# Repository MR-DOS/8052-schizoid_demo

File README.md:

# 8052-schizoid_demo
My own improved implementation of so-called "Schizofreny" 8051 board.You can find the original version [here](http://www.bezstarosti.cz/jungle/schizofreny/schizofreny.htm). 

## Disclaimer
I would like to admit this is a very old project back when I was rather beginner at programming. It somehow survived (or, better to say, did not) being moved across several generations of my computers (about 6 notebooks, 3 desktops, one dead HDD and one HDD encrypted due to ransomware) ranging from PIII-M to 3rd gen i5. I had to visit my parents and search my old computer to get the sources of the PC part of the SW, which I thought have been destroyed long ago.

Since this is an old project, it will receive only very limited support from me.
On the other hand, the project worked and was *usable*. Well, if you call uC with no debug at all usable, that is.

## Brief info
### What this thingumabob consists of
Hardware: AT89C52 with 256B of internal RAM and bootloader (you can in fact use any 8051, just not 80C31), 64 kB of external ROM and 64 kB of external RAM (can be disabled).
Bootloader: Handles all of the programming part and communication with PC via virtual COM port over USB.

Terminal on PC: Communicates with the bootloader over USB. You just have to supply it with the HEX file to be programmed and number of the COM port. Originally, this was used to be integrated into MIDE (8051-centric dead simple IDE).

### How to use it
Hardware: Just build it, no calibration needed.

Bootloader: Program the 80C52 with the bootloader (you need to have a programmer).

Terminal: Use the batch script program.bat. It converts a HEX file into BIN file, sends it to the board and starts the program. It has two arguments, first is the name of the HEX file, second is number of COM port (just a number, like "5", not "COM5").

### MIDE-51 integration
I originally used MIDE-51 for development of the bootloader. Now, I would not recommend the IDE to anyone since it has no autocompletion and next to no connection with the toolchain. However if you wish to use it, here is how to set it up.

* The line with name "execute file" should point to program.bat (8052term.exe and hex2bin.exe have to be in the same directory).
* Parameter 2 specifies number of COM port to which the demoboard is connected.
* MIDE-51 can be downloaded from [here](http://www.opcube.com/home.html#MIDE51).

## Technical info
This "Schizofreny" inspired board uses 128 kB SRAM to emulate 64 kB of ROM and 64 kB of RAM. The program is sent to the board via virtual COM port (CH340G) over USB. Internal bootloader and dedicated circuitry around the 8052 (AT89C52, specifically) handles all of the access to the SRAM during programming. One of the RS232 control signals resets the CPU, another switches it between the bootloader and user mode. Each mode has its own crystal, so the board can be used at any frequency.

The virtual 64 kB RAM portion of the 128 kB SRAM can be disabled so it does not interfere with anything connected to the board. In this mode, ports P1 and P3 are completely free for the user. When the RAM is not disabled, P1 is free, but P3 has P3.6, P3.7 used for RD, WR (access to RAM). The board handles disconnecting of these pins from the header, so it does not interfere with user HW.
To sum it up, you have either 14 or 16 GPIO accessible dependng on the mode (set by jumper).

Sadly, the virtual ROM sits on ports P0 and P2, so it is not possible to use them for anything else. Since the 8052 has 256 bytes of RAM and Flash cannot be reflashed using bootloader, there is no other way to load the program. This is a limitation of the 8051 architecture.

### What was used for the project
The board was made in EAGLE. For those not willing to pay for this shitware to make this board, vector graphics with the board TOP and BOTTOM layers, as well as the schematic, BOM and drawing of placement of parts, are included.

The bootloader was written in C and can be compiled using SDCC. Do not even try with GCC (it does not even have a useable port for 8051, at least not one I'm aware of).

The terminal was written using C (GCC / MinGW) for Windows. It uses RS-232 library from Teunis van Beelen, licensed under GNU GPL, can be found [here](https://www.teuniz.net/RS-232/index.html). If you would like to compile the terminal yourself, you should first check the author's website whether there is a new version of the library.

### Where to find the resources
* The Eagle project is in **HW_eagle**
* The preview of the board, BOM, top and bottom copper layers in PostScript, PDF and SVG and schematics are in **HW_makedata**
* The bootloader is located in **SW_8052_bootloader**. The BIN and HEX files are located in **SW_8052_bootloader/bin/**, sources are in **SW_8052_bootloader/src/**
* The terminal is located in **8052-schizoid_demo/SW_PC_terminal**. The binaries are in **8052-schizoid_demo/SW_PC_terminal/bin**, the sources are in **8052-schizoid_demo/SW_PC_terminal/src**

## Known bugs
* Upon sending the binary to the board, the board responds with some messages saying that the transfer completed. However, prior to that, the board sends one seemingly random character. This is a bug in the main while(1) loop where it waits upon completion of the code loading and then it parses the last character in the buffer as unknown control character and thus is sent back. It has no effect on functionality, but it looks stupid. This should be corrected later.
* There is no image of the finished board. I will add some later.
* It looks like the SVG files are shown correctly in Inkscape, but not in LXDE default image viewer. This should be checked.

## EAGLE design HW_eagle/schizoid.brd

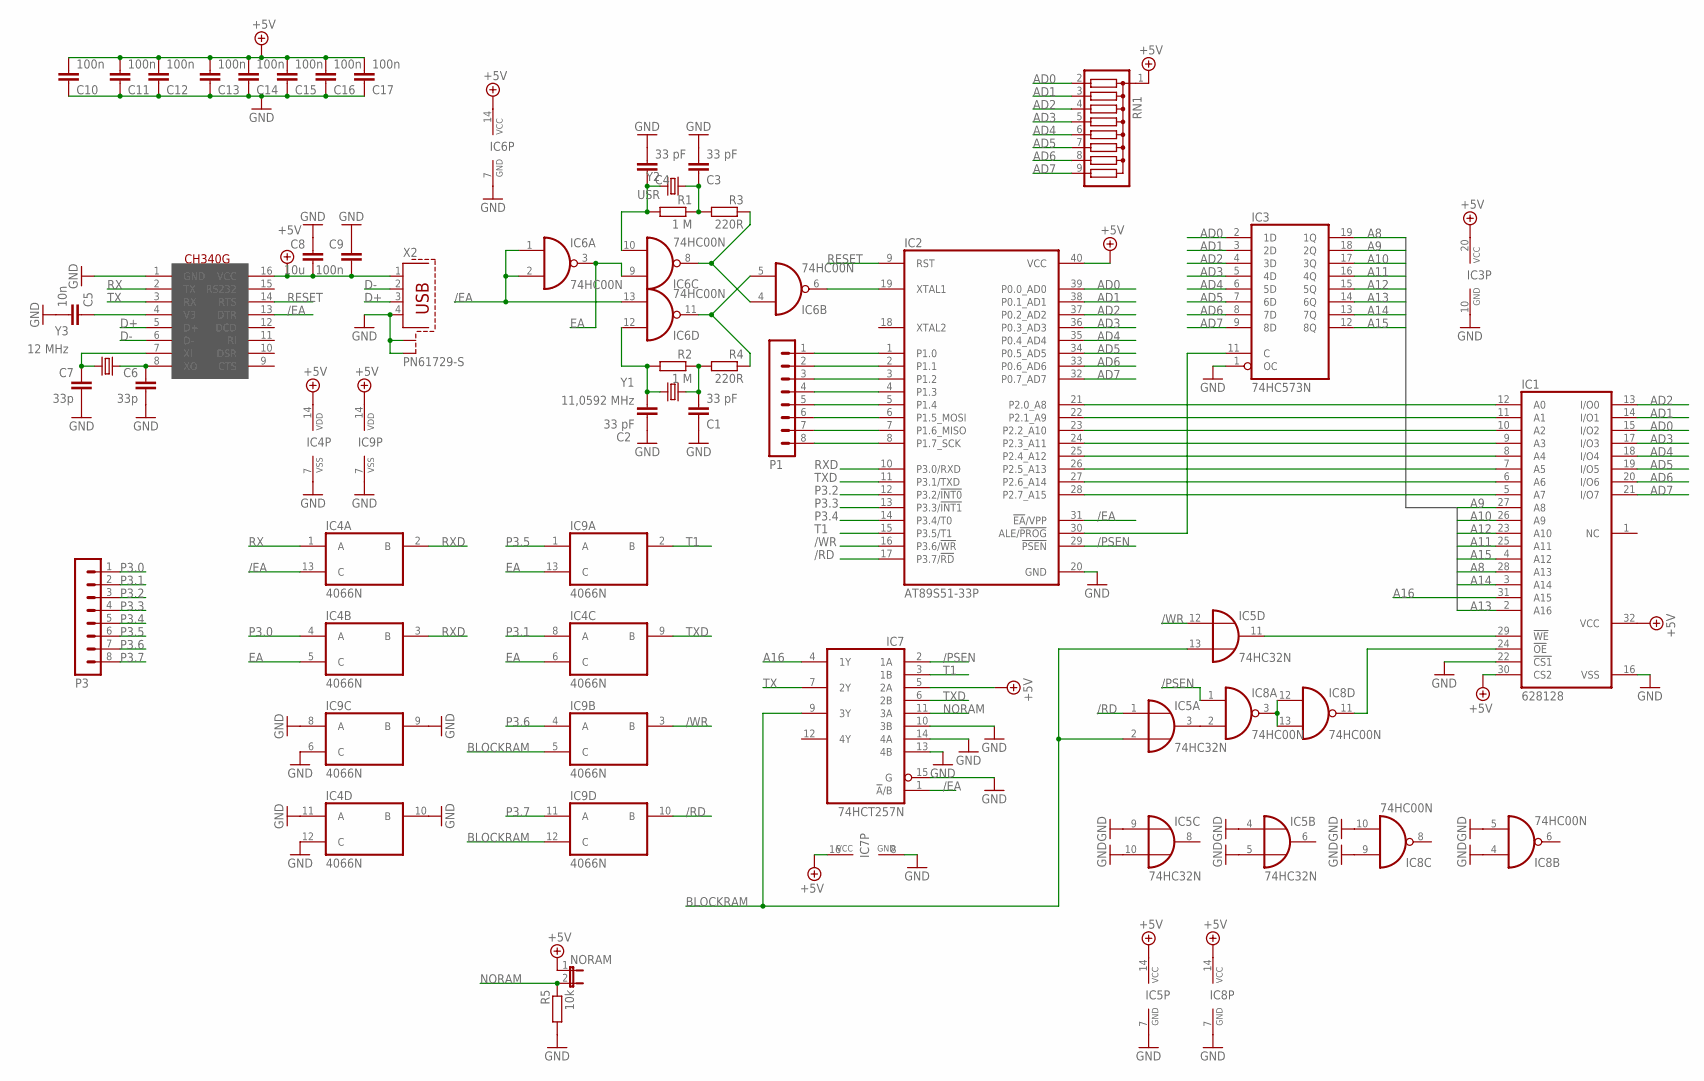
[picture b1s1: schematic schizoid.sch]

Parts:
C1, C2, C3, C4: 33 pF; C025-025X050
C5: 10n; C025-025X050
C6, C7: 33p; C025-025X050
C8: 10u; C025-025X050
C9, C10, C11, C12, C13, C14, C15, C16, C17: 100n; C025-025X050
IC1: 628128; DIL32
IC2: AT89S51-33P; DIL40
IC3: 74HC573N; DIL20
IC4, IC9: 4066N; DIL14
IC5: 74HC32N; DIL14
IC6, IC8: 74HC00N; DIL14
IC7: 74HCT257N; DIL16
NORAM: JP1E; JP1
P1, P3: MA08-1
R1, R2: 1 M; 0207/7
R3, R4: 220R; 0207/7
R5: 10k; 0207/7
RN1: G08R; SIL9
U$1: CH340G; SOIC16
X2: PN61729-S
Y1: 11,0592 MHz; HC49U-V
Y2: USR; HC49U-V
Y3: 12 MHz; HC49U-V

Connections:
+5V: C8.2, C9.2, C10.2, C11.2, C12.2, C13.2, C14.2, C15.2, C16.2, C17.2, IC1.30 (CS2), IC1.32 (VCC), IC2.40 (VCC), IC3.20 (VCC), IC4.14 (VDD), IC5.14 (VCC), IC6.14 (VCC), IC7.5 (2A), IC7.16 (VCC), IC8.14 (VCC), IC9.14 (VDD), NORAM.1, RN1.1, U$1.16 (VCC), X2.1
/EA: IC2.31 (!EA!/VPP), IC4.13 (C), IC6.1 (I0), IC6.2 (I1), IC6.13 (I1), IC7.1 (!A!/B), U$1.13 (DTR)
/PSEN: IC2.29 (!PSEN), IC7.2 (1A), IC8.1 (I0)
/RD: IC2.17 (P3.7/!RD), IC5.1 (I0), IC9.10 (B)
/WR: IC2.16 (P3.6/!WR), IC5.12 (I0), IC9.3 (B)
A8: IC1.28 (A13), IC3.19 (1Q)
A9: IC1.27 (A8), IC3.18 (2Q)
A10: IC1.26 (A9), IC3.17 (3Q)
A11: IC1.25 (A11), IC3.16 (4Q)
A12: IC1.23 (A10), IC3.15 (5Q)
A13: IC1.2 (A16), IC3.14 (6Q)
A14: IC1.3 (A14), IC3.13 (7Q)
A15: IC1.4 (A12), IC3.12 (8Q)
A16: IC1.31 (A15), IC7.4 (1Y)
AD0: IC1.15 (I/O2), IC2.39 (P0.0_AD0), IC3.2 (1D), RN1.2
AD1: IC1.14 (I/O1), IC2.38 (P0.1_AD1), IC3.3 (2D), RN1.3
AD2: IC1.13 (I/O0), IC2.37 (P0.2_AD2), IC3.4 (3D), RN1.4
AD3: IC1.17 (I/O3), IC2.36 (P0.3_AD3), IC3.5 (4D), RN1.5
AD4: IC1.18 (I/O4), IC2.35 (P0.4_AD4), IC3.6 (5D), RN1.6
AD5: IC1.19 (I/O5), IC2.34 (P0.5_AD5), IC3.7 (6D), RN1.7
AD6: IC1.20 (I/O6), IC2.33 (P0.6_AD6), IC3.8 (7D), RN1.8
AD7: IC1.21 (I/O7), IC2.32 (P0.7_AD7), IC3.9 (8D), RN1.9
BLOCKRAM: IC5.2 (I1), IC5.13 (I1), IC7.9 (3Y), IC9.5 (C), IC9.12 (C)
D+: U$1.5 (D+), X2.3
D-: U$1.6 (D-), X2.2
EA: IC4.5 (C), IC4.6 (C), IC6.3 (O), IC6.9 (I0), IC9.13 (C)
GND: C1.1, C2.1, C3.2, C4.2, C5.2, C6.2, C7.2, C8.1, C9.1, C10.1, C11.1, C12.1, C13.1, C14.1, C15.1, C16.1, C17.1, IC1.16 (VSS), IC1.22 (!CS1), IC2.20 (GND), IC3.1 (OC), IC3.10 (GND), IC4.7 (VSS), IC4.10 (B), IC4.11 (A), IC4.12 (C), IC5.4 (I0), IC5.5 (I1), IC5.7 (GND), IC5.9 (I0), IC5.10 (I1), IC6.7 (GND), IC7.8 (GND), IC7.10 (3B), IC7.13 (4B), IC7.14 (4A), IC7.15 (G), IC8.4 (I0), IC8.5 (I1), IC8.7 (GND), IC8.9 (I0), IC8.10 (I1), IC9.6 (C), IC9.7 (VSS), IC9.8 (A), IC9.9 (B), R5.2, U$1.1 (GND), X2.4, X2.S1, X2.S2
unnamed: IC1.12 (A0), IC2.21 (P2.0_A8)
unnamed: IC1.11 (A1), IC2.22 (P2.1_A9)
unnamed: IC1.10 (A2), IC2.23 (P2.2_A10)
unnamed: IC1.9 (A3), IC2.24 (P2.3_A11)
unnamed: IC1.8 (A4), IC2.25 (P2.4_A12)
unnamed: IC1.7 (A5), IC2.26 (P2.5_A13)
unnamed: IC1.6 (A6), IC2.27 (P2.6_A14)
unnamed: IC1.5 (A7), IC2.28 (P2.7_A15)
unnamed: IC2.30 (ALE/!PROG), IC3.11 (C)
unnamed: C3.1, R1.1, R3.2, Y2.1
unnamed: IC2.1 (P1.0), P1.1
unnamed: C1.2, R2.1, R4.2, Y1.1
unnamed: IC2.2 (P1.1), P1.2
unnamed: IC2.3 (P1.2), P1.3
unnamed: IC2.4 (P1.3), P1.4
unnamed: IC2.5 (P1.4), P1.5
unnamed: IC2.6 (P1.5_MOSI), P1.6
unnamed: IC2.7 (P1.6_MISO), P1.7
unnamed: IC5.3 (O), IC8.2 (I1)
unnamed: IC6.4 (I0), IC6.8 (O), R3.1
unnamed: IC8.3 (O), IC8.12 (I0), IC8.13 (I1)
unnamed: IC6.5 (I1), IC6.11 (O), R4.1
unnamed: C2.2, IC6.12 (I0), R2.2, Y1.2
unnamed: IC2.8 (P1.7_SCK), P1.8
unnamed: C4.1, IC6.10 (I1), R1.2, Y2.2
unnamed: IC2.19 (XTAL1), IC6.6 (O)
unnamed: C5.1, U$1.4 (V3)
unnamed: C6.1, U$1.8 (XO), Y3.1
unnamed: C7.1, U$1.7 (XI), Y3.2
unnamed: IC1.29 (!WE), IC5.11 (O)
unnamed: IC1.24 (!OE), IC8.11 (O)
NORAM: IC7.11 (3A), NORAM.2, R5.1
P3.0: IC4.4 (A), P3.1
P3.1: IC4.8 (A), P3.2
P3.2: IC2.12 (P3.2/!INT0), P3.3
P3.3: IC2.13 (P3.3/!INT1), P3.4
P3.4: IC2.14 (P3.4/T0), P3.5
P3.5: IC9.1 (A), P3.6
P3.6: IC9.4 (A), P3.7
P3.7: IC9.11 (A), P3.8
RESET: IC2.9 (RST), U$1.14 (RTS)
RX: IC4.1 (A), U$1.2 (TX)
RXD: IC2.10 (P3.0/RXD), IC4.2 (B), IC4.3 (B)
T1: IC2.15 (P3.5/T1), IC7.3 (1B), IC9.2 (B)
TX: IC7.7 (2Y), U$1.3 (RX)
TXD: IC2.11 (P3.1/TXD), IC4.9 (B), IC7.6 (2B)

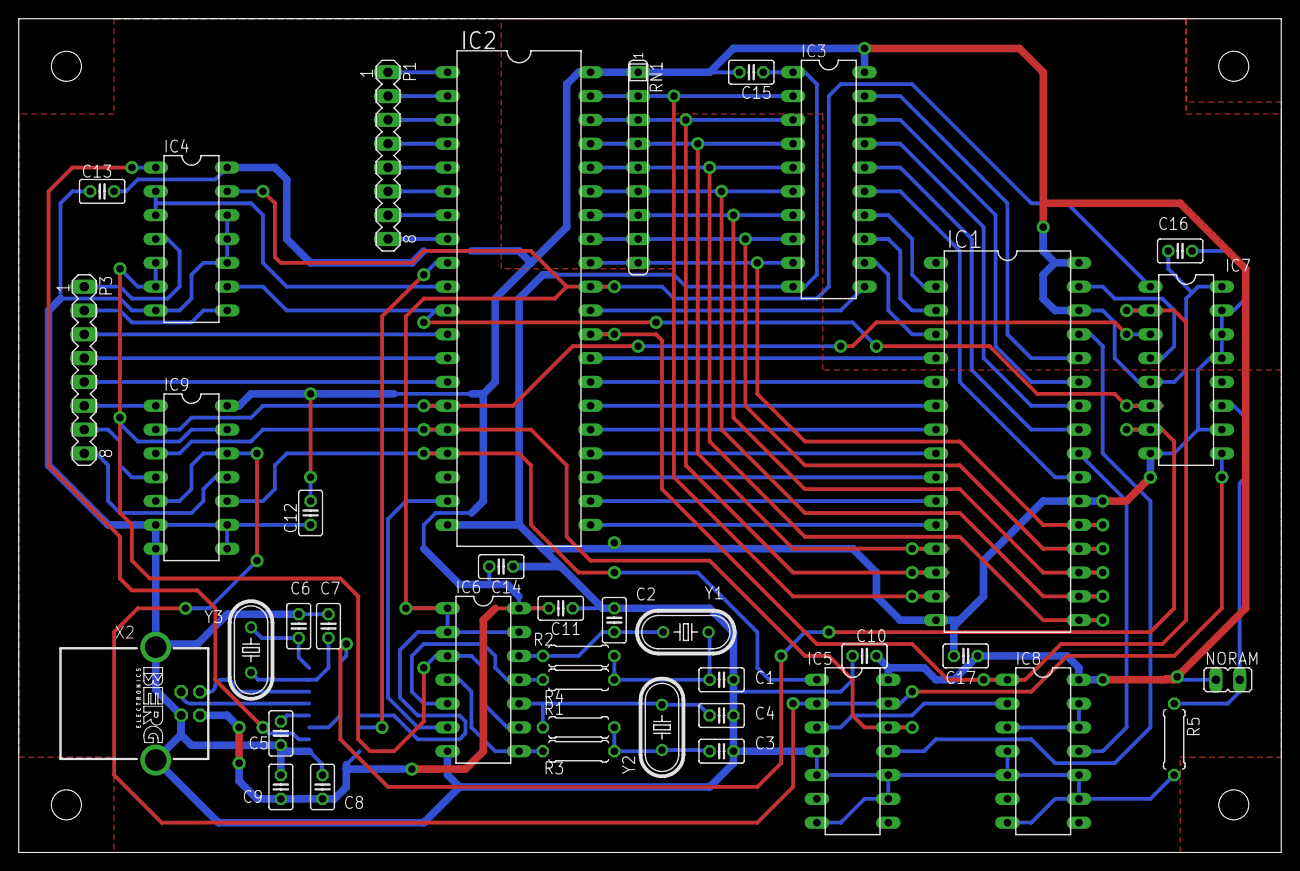
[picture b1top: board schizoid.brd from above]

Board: 2 copper layers, 134.6 x 88.9 mm, 40 parts (1 on the bottom side), 73 nets.

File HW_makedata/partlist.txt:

Partlist

Exported from schizoid.brd at 3/31/2018 4:59 PM

EAGLE Version 7.6.0 Copyright (c) 1988-2016 CadSoft

Assembly variant: 

Part     Value          Package      Library           Position (inch)       Orientation

C1       33 pF          C025-025X050 rcl               (2.95 0.725)          R180
C2       33 pF          C025-025X050 rcl               (2.5 0.975)           R270
C3       33 pF          C025-025X050 rcl               (2.95 0.425)          R0
C4       33 pF          C025-025X050 rcl               (2.95 0.575)          R0
C5       10n            C025-025X050 rcl               (1.1 0.5)             R270
C6       33p            C025-025X050 rcl               (1.175 0.95)          R90
C7       33p            C025-025X050 rcl               (1.3 0.95)            R90
C8       10u            C025-025X050 rcl               (1.275 0.275)         R270
C9       100n           C025-025X050 rcl               (1.1 0.275)           R270
C10      100n           C025-025X050 rcl               (3.55 0.825)          R0
C11      100n           C025-025X050 rcl               (2.275 1.025)         R180
C12      100n           C025-025X050 rcl               (1.225 1.425)         R90
C13      100n           C025-025X050 rcl               (0.35 2.775)          R0
C14      100n           C025-025X050 rcl               (2.025 1.2)           R180
C15      100n           C025-025X050 rcl               (3.075 3.275)         R180
C16      100n           C025-025X050 rcl               (4.875 2.525)         R180
C17      100n           C025-025X050 rcl               (3.975 0.825)         R0
IC1      628128         DIL32        memory-hitachi    (4.15 1.725)          R270
IC2      AT89S51-33P    DIL40        atmel             (2.1 2.325)           R270
IC3      74HC573N       DIL20        74xx-eu           (3.4 2.825)           R270
IC4      4066N          DIL14        40xx              (0.725 2.575)         R270
IC5      74HC32N        DIL14        74xx-eu           (3.5 0.425)           R270
IC6      74HC00N        DIL14        74xx-eu           (1.95 0.725)          R270
IC7      74HCT257N      DIL16        74xx-eu           (4.9 2.025)           R270
IC8      74HC00N        DIL14        74xx-eu           (4.3 0.425)           R270
IC9      4066N          DIL14        40xx              (0.725 1.575)         R270
NORAM                   JP1          jumper            (5.075 0.725)         R270
P1                      MA08-1       con-lstb          (1.55 2.925)          R270
P3                      MA08-1       con-lstb          (0.275 2.025)         R270
R1       1 M            0207/7       rcl               (2.35 0.525)          R180
R2       1 M            0207/7       rcl               (2.35 0.825)          R180
R3       220R           0207/7       rcl               (2.35 0.425)          R0
R4       220R           0207/7       rcl               (2.35 0.725)          R0
R5       10k            0207/7       rcl               (4.85 0.475)          R270
RN1                     SIL9         resistor-sil      (2.6 2.875)           R270
U$1      CH340G         SOIC16       usb-serial        (1.325 0.6)           MR90
X2       PN61729-S      PN61729-S    con-berg          (0.575 0.625)         R270
Y1       11,0592 MHz    HC49U-V      SparkFun-FreqCtrl (2.8 0.925)           R180
Y2       USR            HC49U-V      SparkFun-FreqCtrl (2.7 0.525)           R90
Y3       12 MHz         HC49U-V      SparkFun-FreqCtrl (0.975 0.85)          R270

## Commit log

2018-03-31 Project was improved to contain all necessary information
    Th comments in code were translated to English. BOM and part placement was added. Sources of terminal were found and thus added. README was changed.
2018-03-31 Added link to MIDE-51
    Added link to MIDE-51
2018-03-31 Corrected README
    Link to picture of MIDE setting was corrected.
2018-03-31 Updated README
    Well, now I am surely starting to look like a dick. Apparently, to make new paragrapg, MARKDOWN needs two newlines.
2021-11-23 Create LICENSE
    Added GPLv3 license

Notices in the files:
parts and their libraries:
SparkFun-FreqCtrl: Licensing: Creative Commons ShareAlike 4.0 International - https://creativecommons.org/licenses/by-sa/4.0
